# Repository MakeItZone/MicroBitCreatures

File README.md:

# MicroBitCreatures

Right now, details for this project can be found on our [Forum server](https://forum.makeit.zone/t/micro-bit-creatures-creating-a-kinetic-scene-with-micro-bits/818)

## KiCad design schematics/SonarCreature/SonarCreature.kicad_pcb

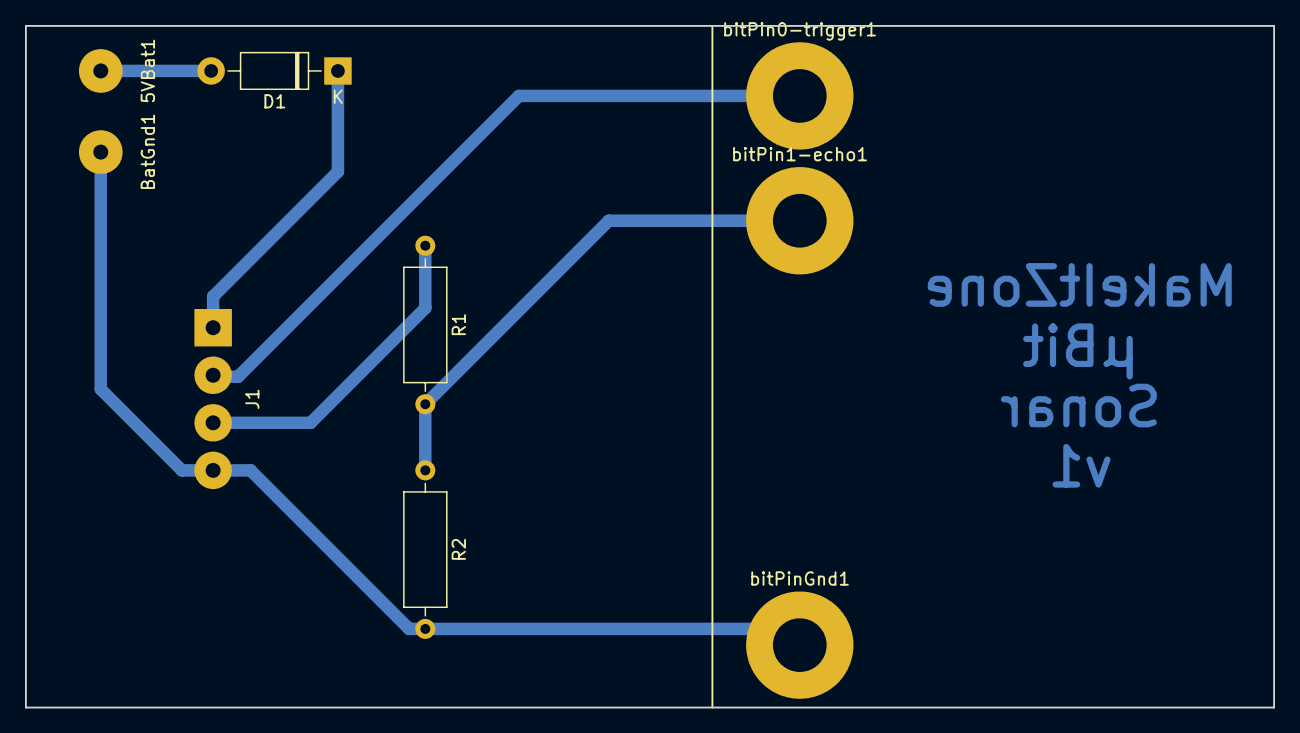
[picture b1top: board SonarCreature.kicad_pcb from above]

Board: 2 copper layers, 100.0 x 54.6 mm, 9 parts (0 on the bottom side), 6 nets.

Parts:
5VBat1: Conn_01x01; SolderWirePad_1x01_Drill1.2mm
BatGnd1: Conn_01x01; SolderWirePad_1x01_Drill1.2mm
D1: 1N4004; D_DO-41_SOD81_P10.16mm_Horizontal
J1: Conn_01x04_Female; SolderWirePad_1x04_P3.81mm_Drill1.2mm
R1: 1k1; R_Axial_DIN0309_L9.0mm_D3.2mm_P12.70mm_Horizontal
R2: 2k2; R_Axial_DIN0309_L9.0mm_D3.2mm_P12.70mm_Horizontal
bitPin0-trigger1, bitPin1-echo1: Conn_01x01; MountingHole_4.3mm_M4_Pad
bitPinGnd1: Conn_01x01; MountingHole_4.3mm_M4_Pad

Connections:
+5V: 5VBat1.1, D1.2
GND: BatGnd1.1, J1.4, R2.2, bitPinGnd1.1
unnamed: D1.1, J1.1
unnamed: J1.2, bitPin0-trigger1.1
unnamed: J1.3, R1.1
unnamed: R1.2, R2.1, bitPin1-echo1.1

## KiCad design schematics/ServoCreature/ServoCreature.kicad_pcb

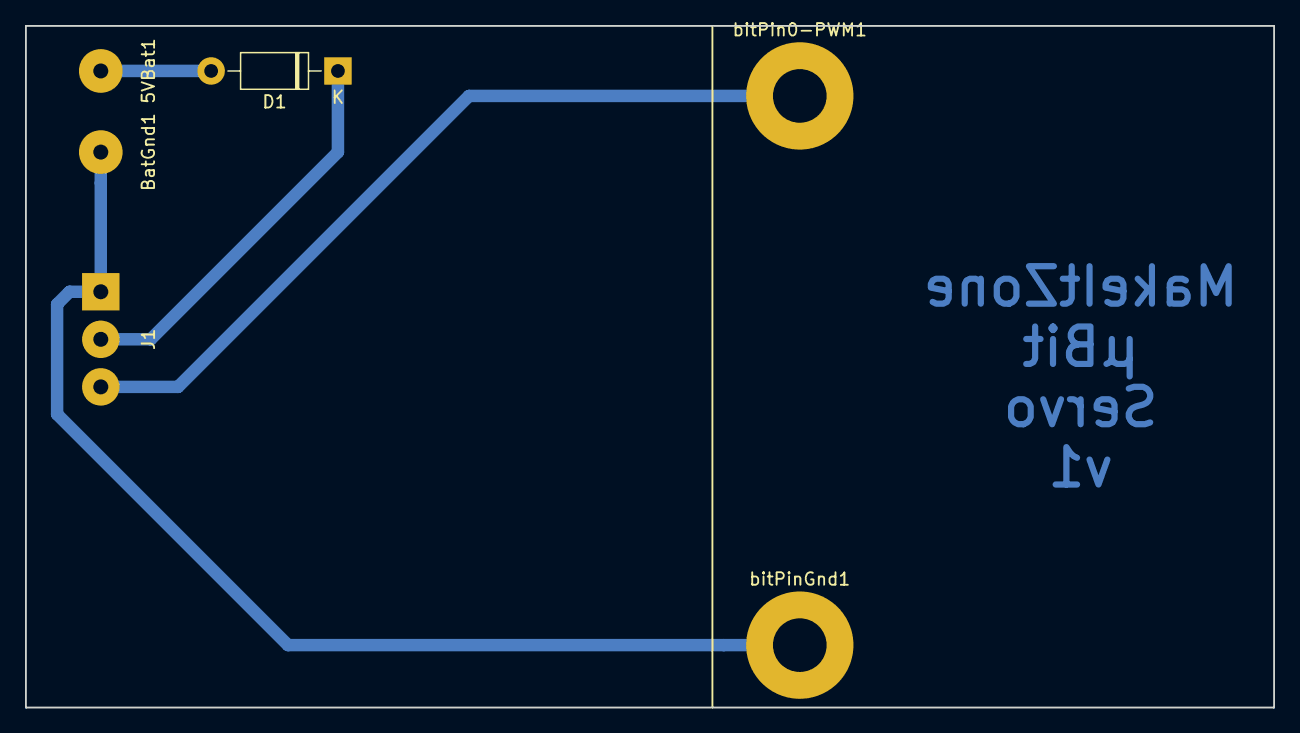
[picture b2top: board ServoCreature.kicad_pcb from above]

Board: 2 copper layers, 100.0 x 54.6 mm, 6 parts (0 on the bottom side), 4 nets.

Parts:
5VBat1: Conn_01x01; SolderWirePad_1x01_Drill1.2mm
BatGnd1: Conn_01x01; SolderWirePad_1x01_Drill1.2mm
D1: 1N4004; D_DO-41_SOD81_P10.16mm_Horizontal
J1: Conn_01x04_Female; SolderWirePad_1x03_P3.81mm_Drill1.2mm
bitPin0-PWM1: Conn_01x01; MountingHole_4.3mm_M4_Pad
bitPinGnd1: Conn_01x01; MountingHole_4.3mm_M4_Pad

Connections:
+5V: 5VBat1.1, D1.2
GND: BatGnd1.1, J1.1, bitPinGnd1.1
unnamed: D1.1, J1.2
unnamed: J1.3, bitPin0-PWM1.1

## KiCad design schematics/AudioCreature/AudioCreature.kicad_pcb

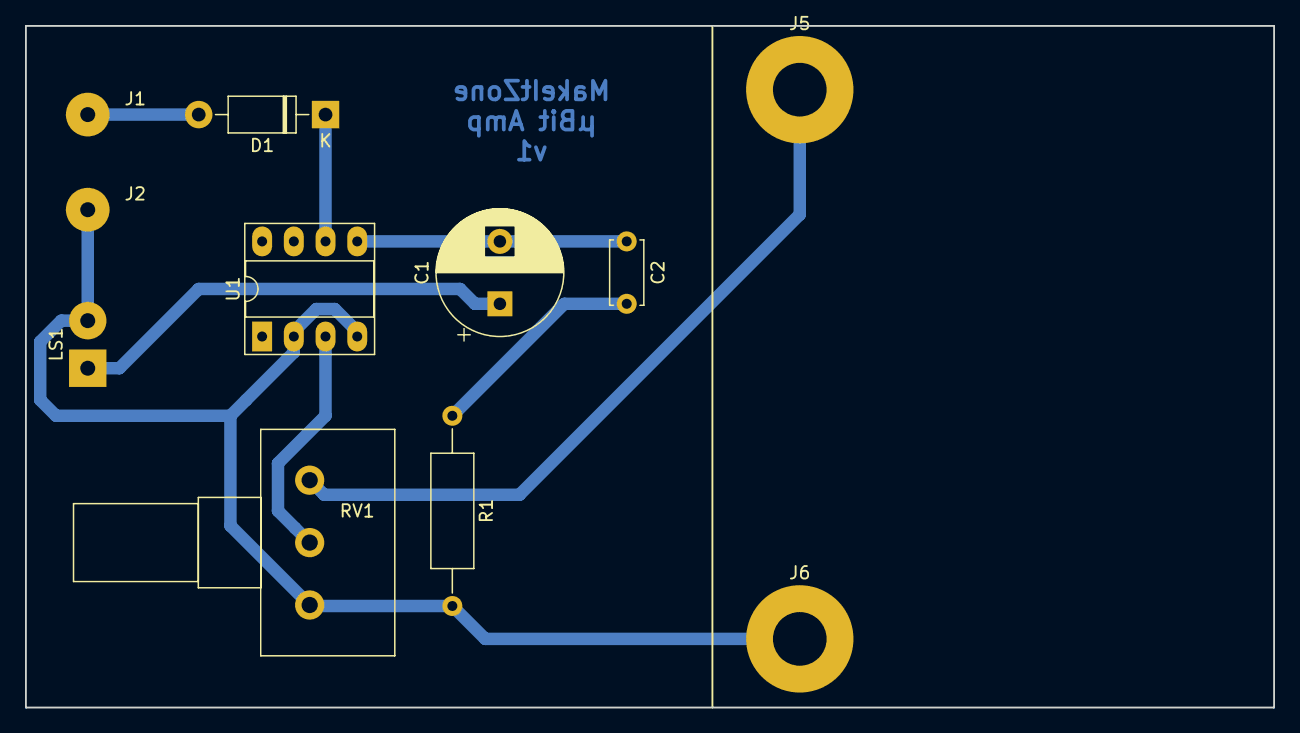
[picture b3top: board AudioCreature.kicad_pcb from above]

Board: 2 copper layers, 100.0 x 54.6 mm, 11 parts (0 on the bottom side), 8 nets.

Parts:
C1: 220uF; CP_Radial_D10.0mm_P5.00mm
C2: 0.022uF; C_Disc_D5.0mm_W2.5mm_P5.00mm
D1: 1N4004; D_DO-41_SOD81_P10.16mm_Horizontal
J1, J2: Conn_01x01; SolderWirePad_1x01_Drill1.2mm
J5, J6: Conn_01x01; MountingHole_4.3mm_M4_Pad
LS1: Speaker; SolderWirePad_1x02_P3.81mm_Drill1.2mm
R1: 10; R_Axial_DIN0309_L9.0mm_D3.2mm_P15.24mm_Horizontal
RV1: 5k; Potentiometer_Alps_RK163_Single_Horizontal
U1: LM386; DIP-8_W7.62mm_Socket_LongPads

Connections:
+5V: D1.2, J1.1
GND: J2.1, J6.1, LS1.2, R1.2, RV1.3, U1.2, U1.4
unnamed: C1.1, LS1.1
unnamed: C1.2, C2.1, U1.5
unnamed: C2.2, R1.1
unnamed: D1.1, U1.6
unnamed: J5.1, RV1.1
unnamed: RV1.2, U1.3

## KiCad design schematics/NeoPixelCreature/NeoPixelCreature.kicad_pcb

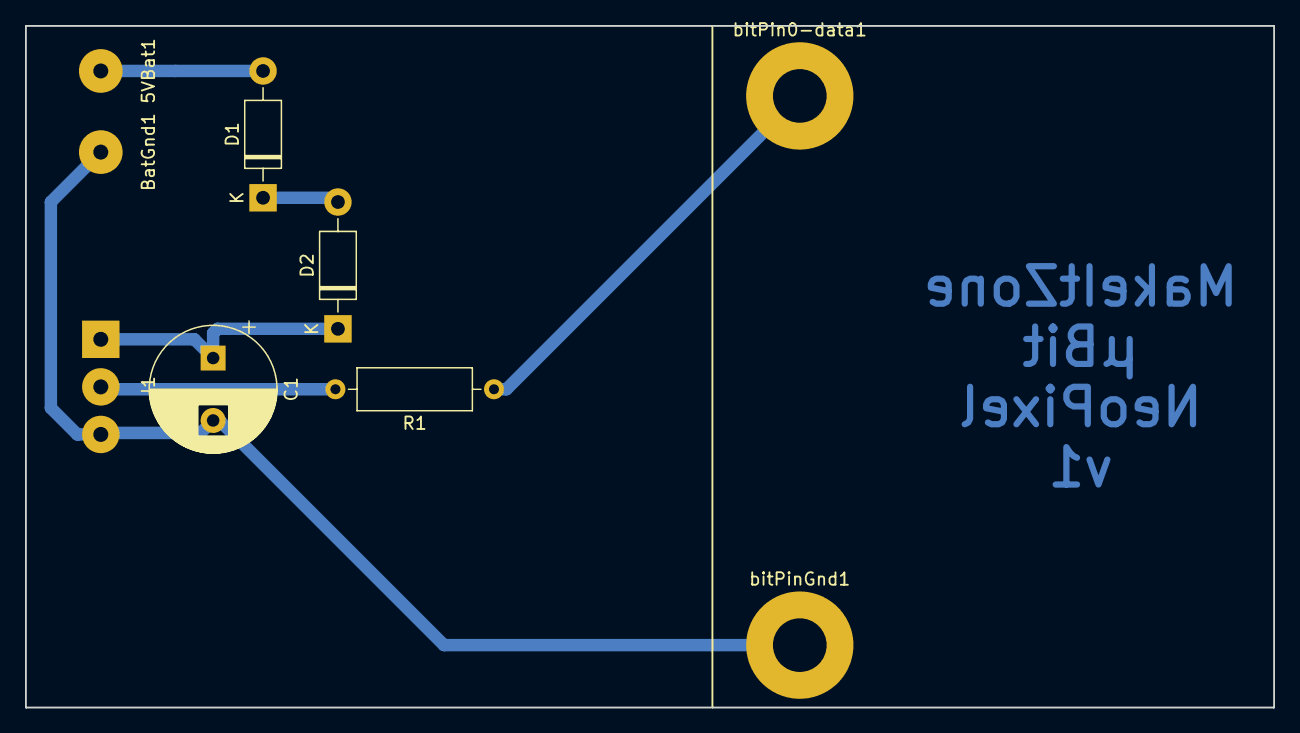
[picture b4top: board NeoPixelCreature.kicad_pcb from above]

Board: 2 copper layers, 100.0 x 54.6 mm, 9 parts (0 on the bottom side), 6 nets.

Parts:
5VBat1: Conn_01x01; SolderWirePad_1x01_Drill1.2mm
BatGnd1: Conn_01x01; SolderWirePad_1x01_Drill1.2mm
C1: 220uF; CP_Radial_D10.0mm_P5.00mm
D1, D2: 1N4004; D_DO-41_SOD81_P10.16mm_Horizontal
J1: Conn_01x04_Female; SolderWirePad_1x03_P3.81mm_Drill1.2mm
R1: 100; R_Axial_DIN0309_L9.0mm_D3.2mm_P12.70mm_Horizontal
bitPin0-data1: Conn_01x01; MountingHole_4.3mm_M4_Pad
bitPinGnd1: Conn_01x01; MountingHole_4.3mm_M4_Pad

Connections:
+5V: 5VBat1.1, D1.2
GND: BatGnd1.1, C1.2, J1.3, bitPinGnd1.1
unnamed: C1.1, D2.1, J1.1
unnamed: D1.1, D2.2
unnamed: J1.2, R1.2
unnamed: R1.1, bitPin0-data1.1

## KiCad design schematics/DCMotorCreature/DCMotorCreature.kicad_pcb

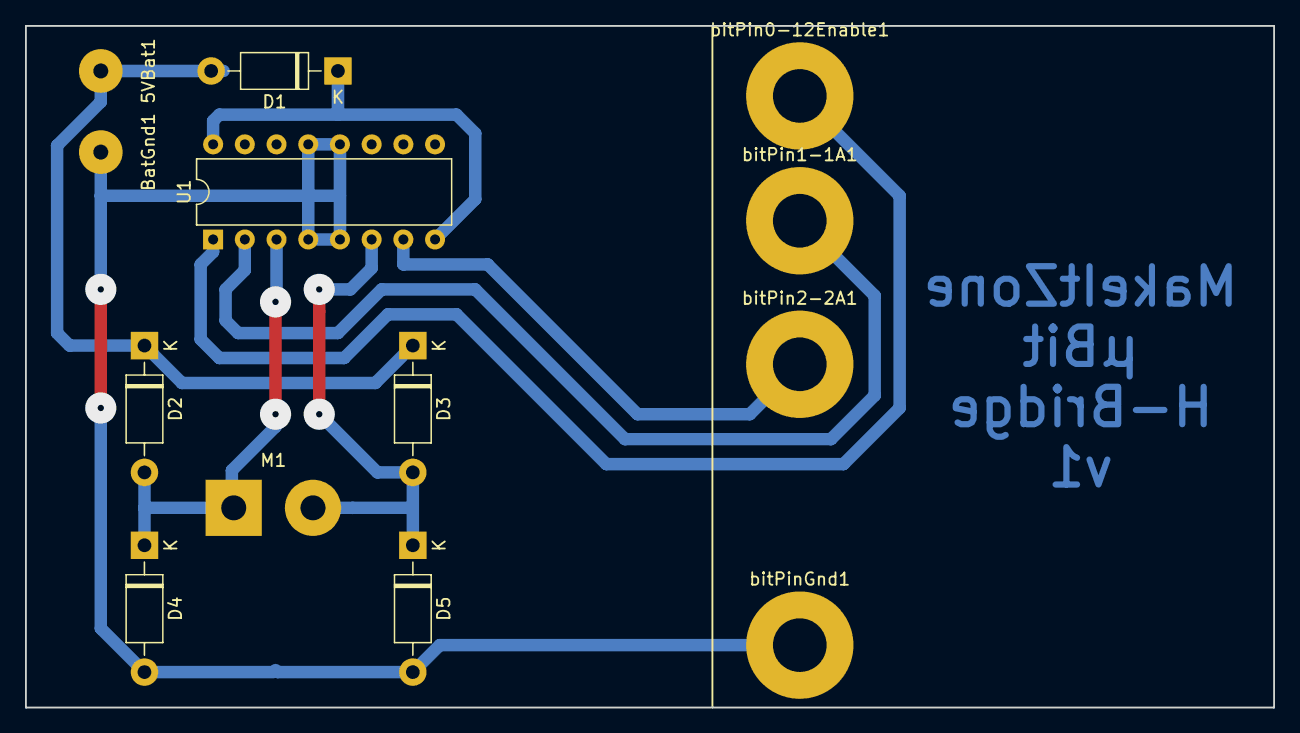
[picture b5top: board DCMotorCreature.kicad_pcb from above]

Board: 2 copper layers, 100.0 x 54.6 mm, 13 parts (0 on the bottom side), 8 nets.

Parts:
5VBat1: Conn_01x01; SolderWirePad_1x01_Drill1.2mm
BatGnd1: Conn_01x01; SolderWirePad_1x01_Drill1.2mm
D1, D2, D3, D4, D5: 1N4004; D_DO-41_SOD81_P10.16mm_Horizontal
M1: Motor_DC; SolderWirePad_1x02_P7.62mm_Drill2mm
U1: L293D; DIP-16_W7.62mm
bitPin0-12Enable1, bitPin1-1A1, bitPin2-2A1: Conn_01x01; MountingHole_4.3mm_M4_Pad
bitPinGnd1: Conn_01x01; MountingHole_4.3mm_M4_Pad

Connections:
+5V: 5VBat1.1, D1.2, D2.1, D3.1
GND: BatGnd1.1, D4.2, D5.2, U1.4, U1.5, U1.9, U1.12, U1.13, bitPinGnd1.1
unnamed: D1.1, U1.8, U1.16
unnamed: D2.2, D4.1, M1.1, U1.3
unnamed: D3.2, D5.1, M1.2, U1.6
unnamed: U1.1, bitPin0-12Enable1.1
unnamed: U1.2, bitPin1-1A1.1
unnamed: U1.7, bitPin2-2A1.1

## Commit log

2018-12-03 initialization
2018-12-03 adding lesson plan
2018-12-03 images and updates
